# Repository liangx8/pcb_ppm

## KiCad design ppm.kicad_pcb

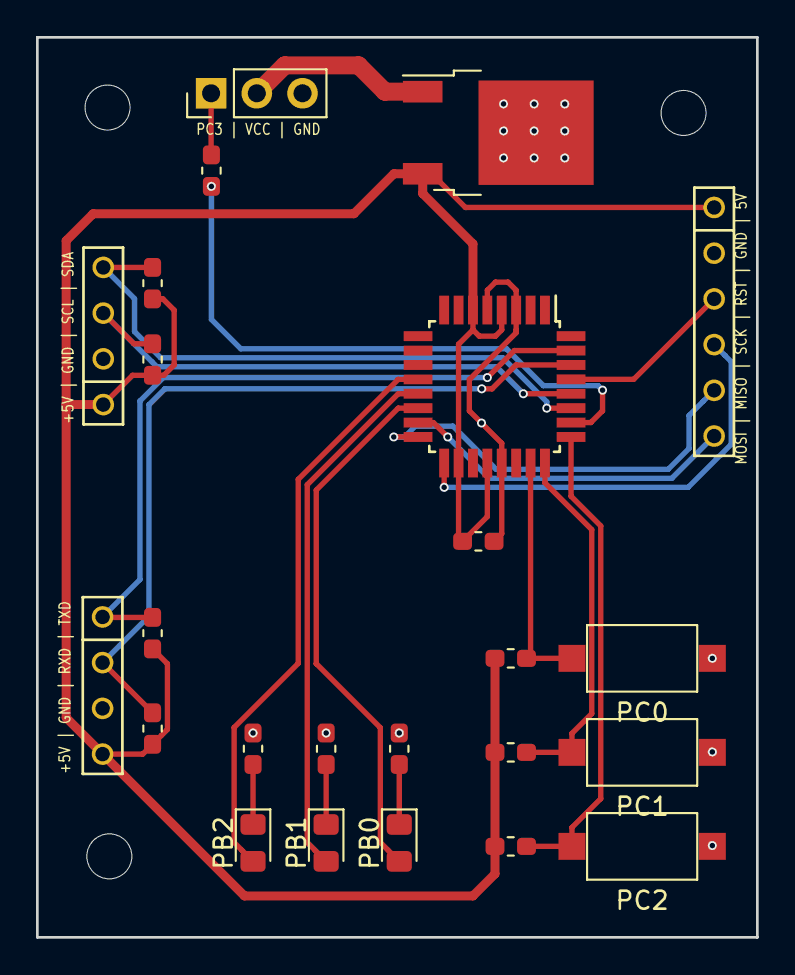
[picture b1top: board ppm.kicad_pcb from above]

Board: 2 copper layers, 40.0 x 50.0 mm, 24 parts (0 on the bottom side), 22 nets.

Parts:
C1: C; C_0603_1608Metric_Pad1.05x0.95mm_HandSolder
D1: PB0; LED_0805_2012Metric_Pad1.15x1.40mm_HandSolder
D2: PB1; LED_0805_2012Metric_Pad1.15x1.40mm_HandSolder
D3: PB2; LED_0805_2012Metric_Pad1.15x1.40mm_HandSolder
J1, J2: Conn_01x04; conn-4x2.54mm
J3: Conn_01x03; PinHeader_1x03_P2.54mm_Vertical
J4: Conn_01x06; conn-6x2.54mm
R1, R2, R3, R4, R8: R; R_0603_1608Metric_Pad1.05x0.95mm_HandSolder
R5, R6, R7, R9, R10, R11: 1K; R_0603_1608Metric_Pad1.05x0.95mm_HandSolder
SW1: PC2; SW_SPST_CK_RS282G05A3
SW2: PC1; SW_SPST_CK_RS282G05A3
SW3: PC0; SW_SPST_CK_RS282G05A3
U1: ATmega48-20AU; TQFP-32_7x7mm_P0.8mm
U2: KA78M05_TO252; TO-252-2

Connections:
+5V: C1.1, J1.1, J2.4, J4.1, R1.1, R2.1, R3.1, R4.1, R5.1, R6.1, R7.1, U1.4, U1.6, U1.18, U1.20, U2.3
/PC0: R7.2, SW3.1, U1.23
/PC1: R6.2, SW2.1, U1.24
/PC2: R5.2, SW1.1, U1.25
/PC3: R8.2, U1.26
/RXD: J2.2, R2.2, U1.30
/SCL: J1.3, R4.2, U1.28
/SDA: J1.4, R3.2, U1.27
/TXD: J2.1, R1.2, U1.31
/led1: D1.2, U1.14
/led2: D2.2, U1.13
/led3: D3.2, U1.12
/miso: J4.5, U1.16
/mosi: J4.6, U1.15
/rst: J4.3, U1.29
/sck: J4.4, U1.17
GND: C1.2, J1.2, J2.3, J3.3, J4.2, R9.1, R10.1, R11.1, SW1.2, SW2.2, SW3.2, U1.3, U1.5, U1.21, U2.2
unnamed: D1.1, R9.2
unnamed: D2.1, R10.2
unnamed: D3.1, R11.2
unnamed: J3.1, R8.1
VCC: J3.2, U2.1

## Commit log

2019-11-11 init ...
2019-11-12 done
